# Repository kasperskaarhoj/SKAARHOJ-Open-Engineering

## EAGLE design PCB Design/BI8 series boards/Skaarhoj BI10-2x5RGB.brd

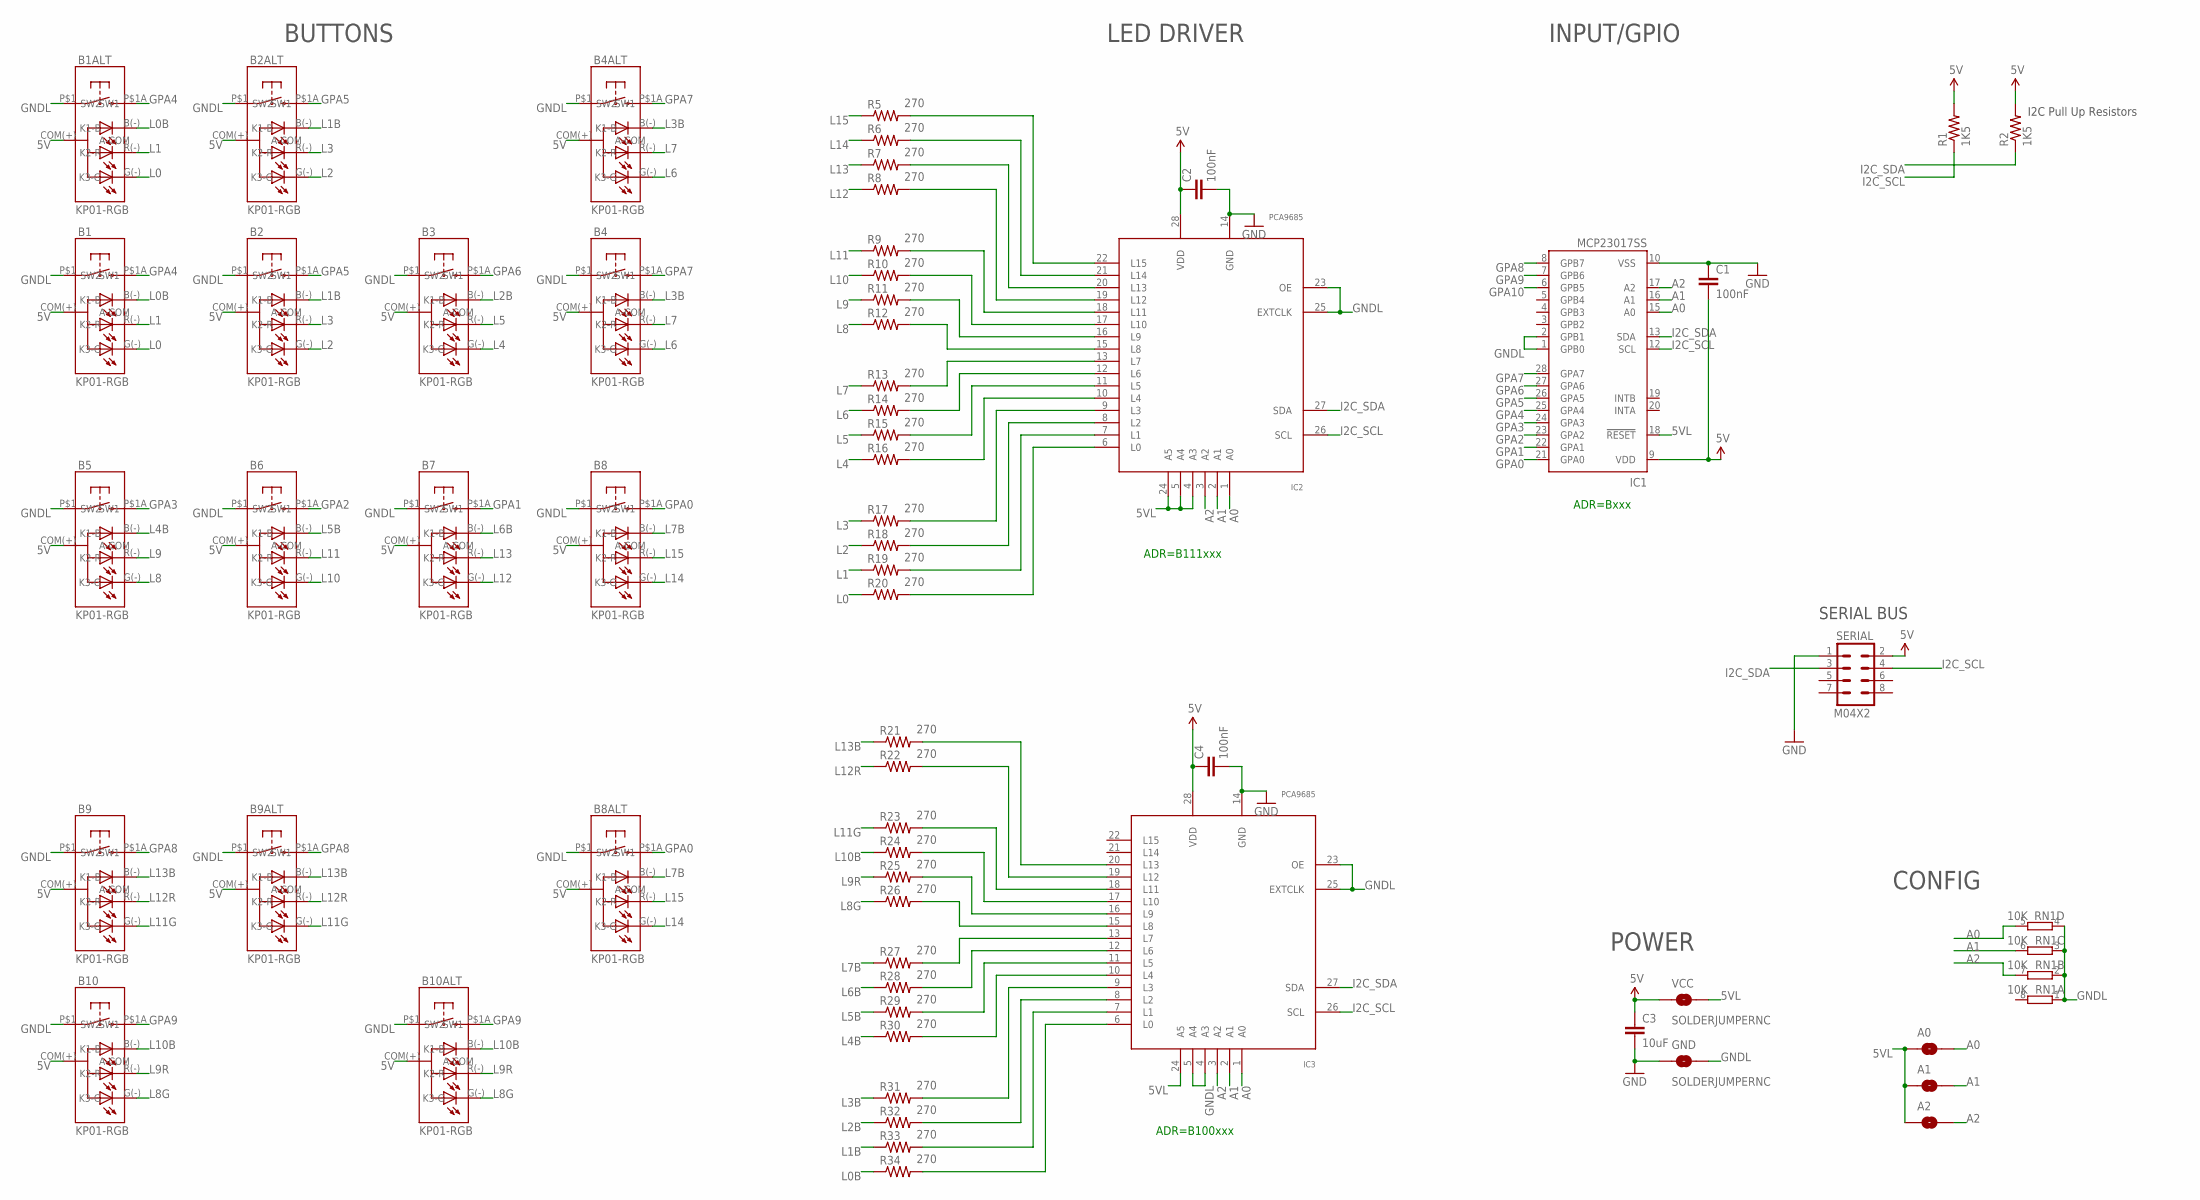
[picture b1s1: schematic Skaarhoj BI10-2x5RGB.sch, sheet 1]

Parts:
A0, A1, A2: SOLDERJUMPERNC; SJ_2S
B1, B1ALT, B2, B2ALT, B3, B4, B4ALT, B5, B6, B7, B8, B8ALT, B9, B9ALT, B10, B10ALT: KP01-RGB; NKK-KP01
C1, C2, C4: 100nF; 0603-CAP
C3: 10uF; 0805
GND: SOLDERJUMPERNC; SJ_2S
IC1: MCP23017SS; SSOP28; MPN MCP23017-E/SS
IC2, IC3: PCA9685; TSSOP28
R1, R2: 1K5; 0603-RES
R5, R6, R7, R8, R9, R10, R11, R12, R13, R14, R15, R16, R17, R18, R19, R20, R21, R22, R23, R24, R25, R26, R27, R28, R29, R30, R31, R32, R33, R34: 270; 0603-RES
RN1: 10K; CAY16_HAND
SERIAL: M04X2; 2X4
VCC: SOLDERJUMPERNC; SJ_2S

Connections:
5V: B1.COM(+) (A-COM), B1ALT.COM(+) (A-COM), B2.COM(+) (A-COM), B2ALT.COM(+) (A-COM), B3.COM(+) (A-COM), B4.COM(+) (A-COM), B4ALT.COM(+) (A-COM), B5.COM(+) (A-COM), B6.COM(+) (A-COM), B7.COM(+) (A-COM), B8.COM(+) (A-COM), B8ALT.COM(+) (A-COM), B9.COM(+) (A-COM), B9ALT.COM(+) (A-COM), B10.COM(+) (A-COM), B10ALT.COM(+) (A-COM), C1.2, C2.1, C3.1, C4.1, IC1.9 (VDD), IC2.28 (VDD), IC3.28 (VDD), R1.2, R2.2, SERIAL.2, VCC.1
5VL: A0.1, A1.1, A2.1, IC1.18 (!RESET), IC2.4 (A3), IC2.5 (A4), IC2.24 (A5), IC3.24 (A5), VCC.2
A0: A0.2, IC1.15 (A0), IC2.1 (A0), IC3.1 (A0), RN1.5 (2)
A1: A1.2, IC1.16 (A1), IC2.2 (A1), IC3.2 (A1), RN1.6 (2)
A2: A2.2, IC1.17 (A2), IC2.3 (A2), IC3.3 (A2), RN1.7 (2)
GND: C1.1, C2.2, C3.2, C4.2, GND.1, IC1.10 (VSS), IC2.14 (GND), IC3.14 (GND), SERIAL.1
GNDL: B1.P$1 (SW1), B1ALT.P$1 (SW1), B2.P$1 (SW1), B2ALT.P$1 (SW1), B3.P$1 (SW1), B4.P$1 (SW1), B4ALT.P$1 (SW1), B5.P$1 (SW1), B6.P$1 (SW1), B7.P$1 (SW1), B8.P$1 (SW1), B8ALT.P$1 (SW1), B9.P$1 (SW1), B9ALT.P$1 (SW1), B10.P$1 (SW1), B10ALT.P$1 (SW1), GND.2, IC1.1 (GPB0), IC1.2 (GPB1), IC2.23 (OE), IC2.25 (EXTCLK), IC3.4 (A3), IC3.5 (A4), IC3.23 (OE), IC3.25 (EXTCLK), RN1.1, RN1.2 (1), RN1.3 (1), RN1.4 (1)
GPA0: B8.P$1A (SW2), B8ALT.P$1A (SW2), IC1.21 (GPA0)
GPA1: B7.P$1A (SW2), IC1.22 (GPA1)
GPA2: B6.P$1A (SW2), IC1.23 (GPA2)
GPA3: B5.P$1A (SW2), IC1.24 (GPA3)
GPA4: B1.P$1A (SW2), B1ALT.P$1A (SW2), IC1.25 (GPA4)
GPA5: B2.P$1A (SW2), B2ALT.P$1A (SW2), IC1.26 (GPA5)
GPA6: B3.P$1A (SW2), IC1.27 (GPA6)
GPA7: B4.P$1A (SW2), B4ALT.P$1A (SW2), IC1.28 (GPA7)
GPA8: B9.P$1A (SW2), B9ALT.P$1A (SW2), IC1.8 (GPB7)
GPA9: B10.P$1A (SW2), B10ALT.P$1A (SW2), IC1.7 (GPB6)
GPA10: IC1.6 (GPB5)
I2C_SCL: IC1.12 (SCL), IC2.26 (SCL), IC3.26 (SCL), R1.1, SERIAL.4
I2C_SDA: IC1.13 (SDA), IC2.27 (SDA), IC3.27 (SDA), R2.1, SERIAL.3
L0: B1.G(-) (K3-G), B1ALT.G(-) (K3-G), R20.1
L0B: B1.B(-) (K1-B), B1ALT.B(-) (K1-B), R34.1
L1: B1.R(-) (K2-R), B1ALT.R(-) (K2-R), R19.1
L1B: B2.B(-) (K1-B), B2ALT.B(-) (K1-B), R33.1
L2: B2.G(-) (K3-G), B2ALT.G(-) (K3-G), R18.1
L2B: B3.B(-) (K1-B), R32.1
L3: B2.R(-) (K2-R), B2ALT.R(-) (K2-R), R17.1
L3B: B4.B(-) (K1-B), B4ALT.B(-) (K1-B), R31.1
L4: B3.G(-) (K3-G), R16.1
L4B: B5.B(-) (K1-B), R30.1
L5: B3.R(-) (K2-R), R15.1
L5B: B6.B(-) (K1-B), R29.1
L6: B4.G(-) (K3-G), B4ALT.G(-) (K3-G), R14.1
L6B: B7.B(-) (K1-B), R28.1
L7: B4.R(-) (K2-R), B4ALT.R(-) (K2-R), R13.1
L7B: B8.B(-) (K1-B), B8ALT.B(-) (K1-B), R27.1
L8: B5.G(-) (K3-G), R12.1
L8G: B10.G(-) (K3-G), B10ALT.G(-) (K3-G), R26.1
L9: B5.R(-) (K2-R), R11.1
L9R: B10.R(-) (K2-R), B10ALT.R(-) (K2-R), R25.1
L10: B6.G(-) (K3-G), R10.1
L10B: B10.B(-) (K1-B), B10ALT.B(-) (K1-B), R24.1
L11: B6.R(-) (K2-R), R9.1
L11G: B9.G(-) (K3-G), B9ALT.G(-) (K3-G), R23.1
L12: B7.G(-) (K3-G), R8.1
L12R: B9.R(-) (K2-R), B9ALT.R(-) (K2-R), R22.1
L13: B7.R(-) (K2-R), R7.1
L13B: B9.B(-) (K1-B), B9ALT.B(-) (K1-B), R21.1
L14: B8.G(-) (K3-G), B8ALT.G(-) (K3-G), R6.1
L15: B8.R(-) (K2-R), B8ALT.R(-) (K2-R), R5.1
unnamed: IC3.13 (L7), R27.2
unnamed: IC3.12 (L6), R28.2
unnamed: IC2.13 (L7), R13.2
unnamed: IC2.12 (L6), R14.2
unnamed: IC3.11 (L5), R29.2
unnamed: IC2.11 (L5), R15.2
unnamed: IC2.10 (L4), R16.2
unnamed: IC2.9 (L3), R17.2
unnamed: IC2.8 (L2), R18.2
unnamed: IC2.7 (L1), R19.2
unnamed: IC3.10 (L4), R30.2
unnamed: IC3.9 (L3), R31.2
unnamed: IC3.8 (L2), R32.2
unnamed: IC3.7 (L1), R33.2
unnamed: IC3.6 (L0), R34.2
unnamed: IC3.15 (L8), R26.2
unnamed: IC2.6 (L0), R20.2
unnamed: IC2.15 (L8), R12.2
unnamed: IC2.16 (L9), R11.2
unnamed: IC2.17 (L10), R10.2
unnamed: IC2.18 (L11), R9.2
unnamed: IC2.19 (L12), R8.2
unnamed: IC2.20 (L13), R7.2
unnamed: IC2.21 (L14), R6.2
unnamed: IC2.22 (L15), R5.2
unnamed: IC3.16 (L9), R25.2
unnamed: IC3.17 (L10), R24.2
unnamed: IC3.18 (L11), R23.2
unnamed: IC3.19 (L12), R22.2
unnamed: IC3.20 (L13), R21.2

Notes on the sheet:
I2C Pull Up Resistors
SERIAL BUS
ADR=B111xxx
ADR=Bxxx
BUTTONS
LED DRIVER
INPUT/GPIO
POWER
CONFIG
ADR=B100xxx

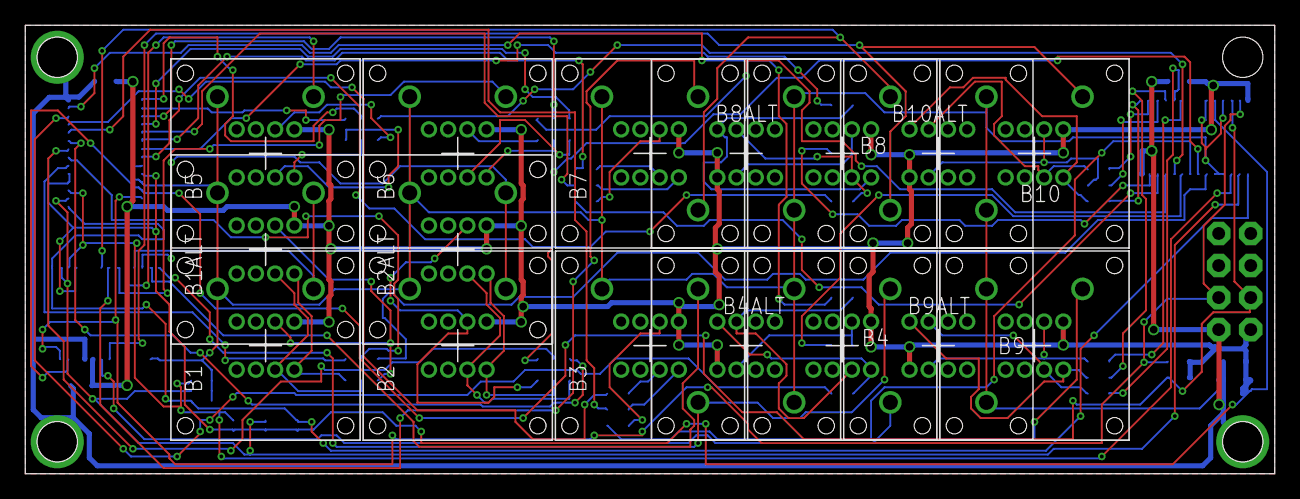
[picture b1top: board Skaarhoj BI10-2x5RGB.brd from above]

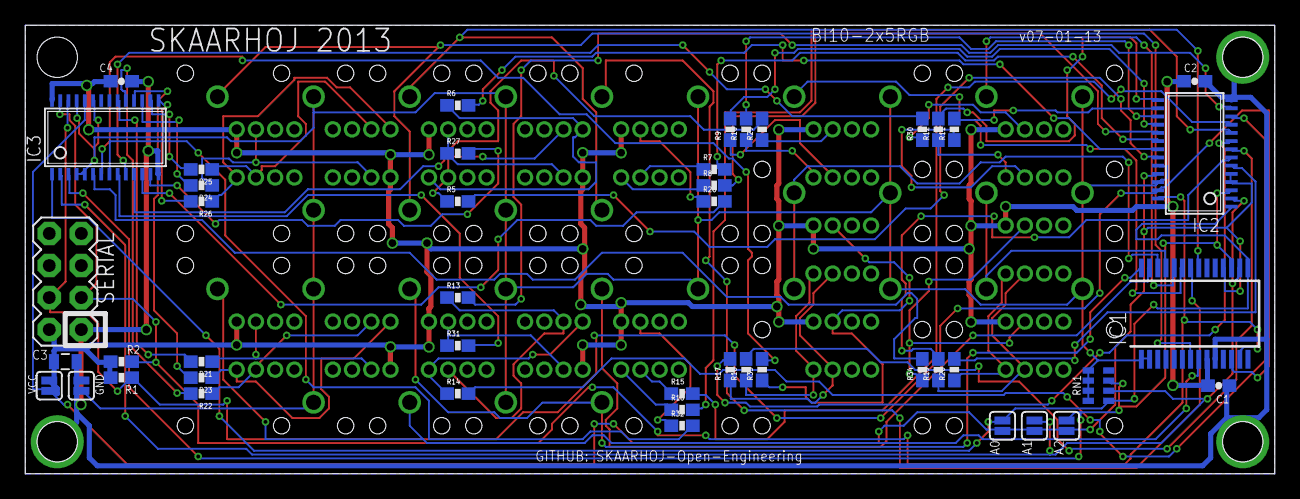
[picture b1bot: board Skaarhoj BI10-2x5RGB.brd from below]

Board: 2 copper layers, 99.1 x 35.6 mm, 62 parts (46 on the bottom side), 79 nets.

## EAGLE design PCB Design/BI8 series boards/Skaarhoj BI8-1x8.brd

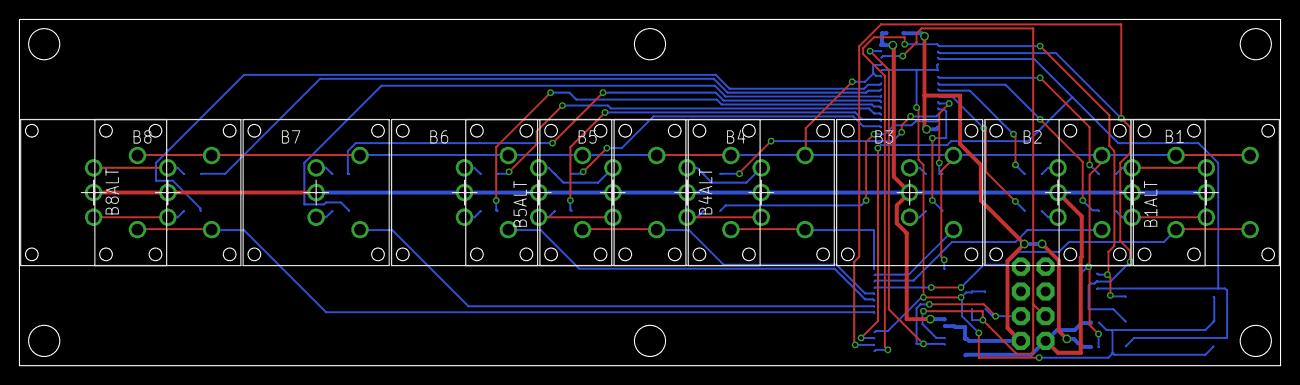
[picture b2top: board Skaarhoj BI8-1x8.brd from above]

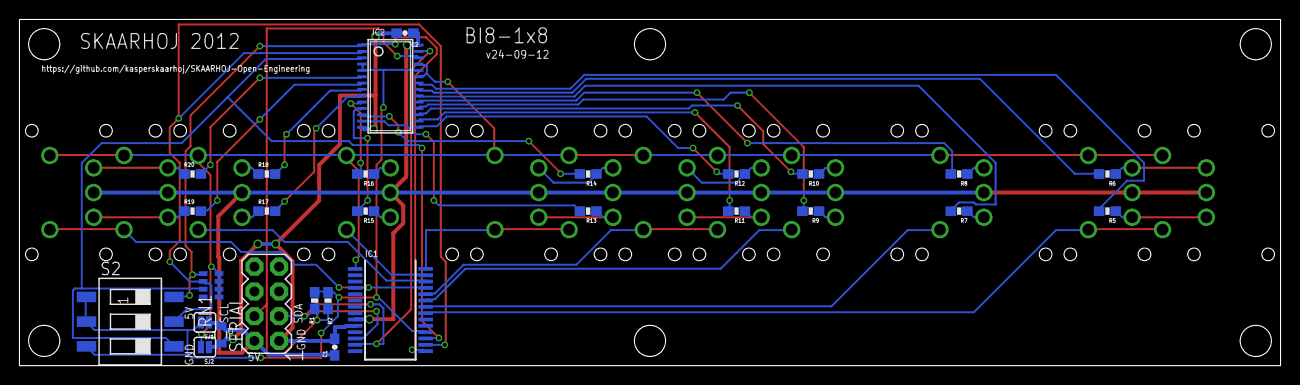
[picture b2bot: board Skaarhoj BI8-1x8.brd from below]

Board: 2 copper layers, 129.5 x 35.6 mm, 40 parts (28 on the bottom side), 49 nets.

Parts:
B1, B1ALT, B2, B3, B4, B4ALT, B5, B5ALT, B6, B7, B8, B8ALT: LP11-B"; LP11
C1, C2: 100nF; 0603-CAP
C3: 10uF; 0805
IC1: MCP23017SS; SSOP28
IC2: PCA9685; TSSOP28
R1, R2: 10K; 0603-RES
R5, R6, R7, R8, R9, R10, R11, R12, R13, R14, R15, R16, R17, R18, R19, R20: 270; 0603-RES
RN1: 10K; CAY16_HAND
S2: SWS003; SMS-003
SERIAL: M04X2; 2X4
SJ1, SJ2: SOLDERJUMPERNC; SJ_2S

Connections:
5V: B1.COM, B1ALT.COM, B2.COM, B3.COM, B4.COM, B4ALT.COM, B5.COM, B5ALT.COM, B6.COM, B7.COM, B8.COM, B8ALT.COM, C1.2, C2.1, C3.1, IC1.9, IC2.28, SERIAL.2, SJ1.1
5VL: IC1.18, IC2.4, IC2.5, IC2.24, R1.1, R2.1, S2.1, S2.2, S2.3, SJ1.2
A0: IC1.15, IC2.1, RN1.5, S2.6
A1: IC1.16, IC2.2, RN1.6, S2.5
A2: IC1.17, IC2.3, RN1.7, S2.4
GND: C1.1, C2.2, C3.2, IC1.10, IC2.14, SERIAL.1, SJ2.1
GNDL: B1.P$4, B1ALT.P$4, B2.P$4, B3.P$4, B4.P$4, B4ALT.P$4, B5.P$4, B5ALT.P$4, B6.P$4, B7.P$4, B8.P$4, B8ALT.P$4, IC1.1, IC2.23, IC2.25, RN1.1, RN1.2, RN1.3, RN1.4, SJ2.2
GPA0: B8.P$5, B8ALT.P$5, IC1.21
GPA1: B7.P$5, IC1.22
GPA2: B6.P$5, IC1.23
GPA3: B5.P$5, B5ALT.P$5, IC1.24
GPA4: B1.P$5, B1ALT.P$5, IC1.25
GPA5: B2.P$5, IC1.26
GPA6: B3.P$5, IC1.27
GPA7: B4.P$5, B4ALT.P$5, IC1.28
I2C_SCL: IC1.12, IC2.26, R2.2, SERIAL.4
I2C_SDA: IC1.13, IC2.27, R1.2, SERIAL.3
L0: B1.P$2, B1ALT.P$2, R20.1
L1: B1.P$3, B1ALT.P$3, R19.1
L2: B2.P$2, R18.1
L3: B2.P$3, R17.1
L4: B3.P$2, R16.1
L5: B3.P$3, R15.1
L6: B4.P$2, B4ALT.P$2, R14.1
L7: B4.P$3, B4ALT.P$3, R13.1
L8: B5.P$2, B5ALT.P$2, R12.1
L9: B5.P$3, B5ALT.P$3, R11.1
L10: B6.P$2, R10.1
L11: B6.P$3, R9.1
L12: B7.P$2, R8.1
L13: B7.P$3, R7.1
L14: B8.P$2, B8ALT.P$2, R6.1
L15: B8.P$3, B8ALT.P$3, R5.1
unnamed: IC2.13, R13.2
unnamed: IC2.12, R14.2
unnamed: IC2.11, R15.2
unnamed: IC2.10, R16.2
unnamed: IC2.9, R17.2
unnamed: IC2.8, R18.2
unnamed: IC2.7, R19.2
unnamed: IC2.6, R20.2
unnamed: IC2.15, R12.2
unnamed: IC2.16, R11.2
unnamed: IC2.17, R10.2
unnamed: IC2.18, R9.2
unnamed: IC2.19, R8.2
unnamed: IC2.20, R7.2
unnamed: IC2.21, R6.2
unnamed: IC2.22, R5.2

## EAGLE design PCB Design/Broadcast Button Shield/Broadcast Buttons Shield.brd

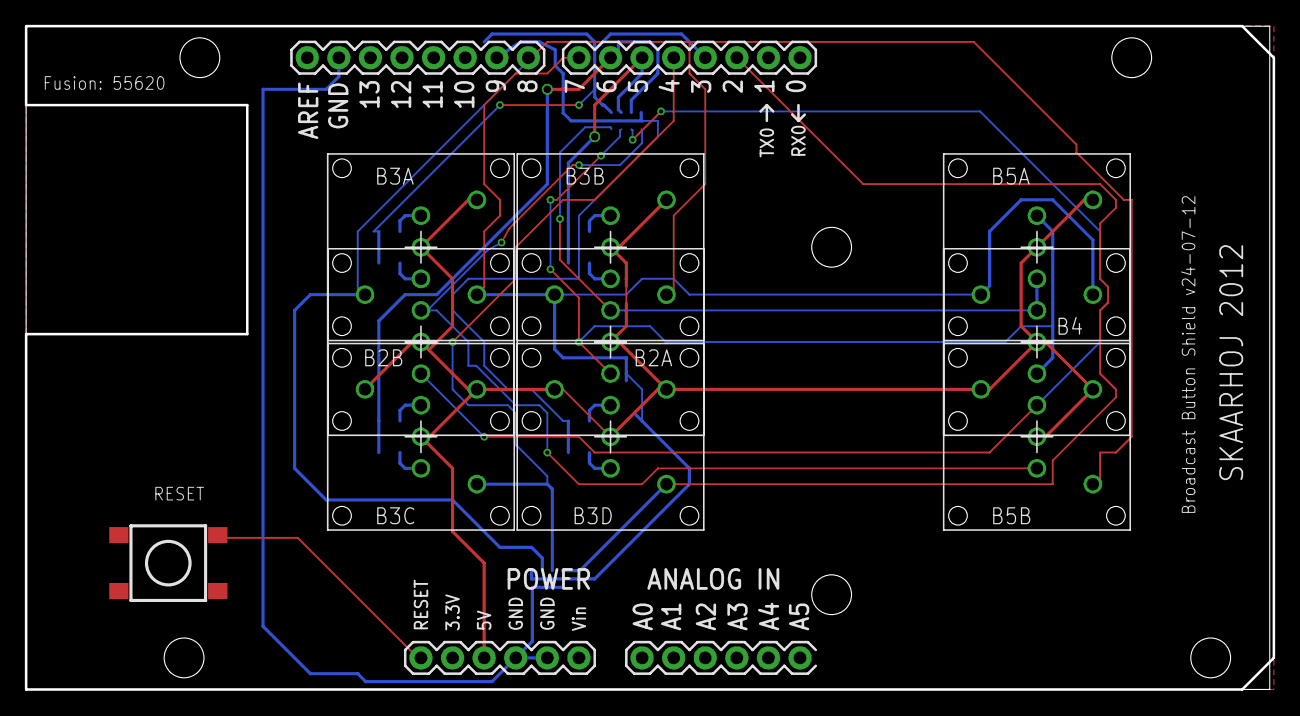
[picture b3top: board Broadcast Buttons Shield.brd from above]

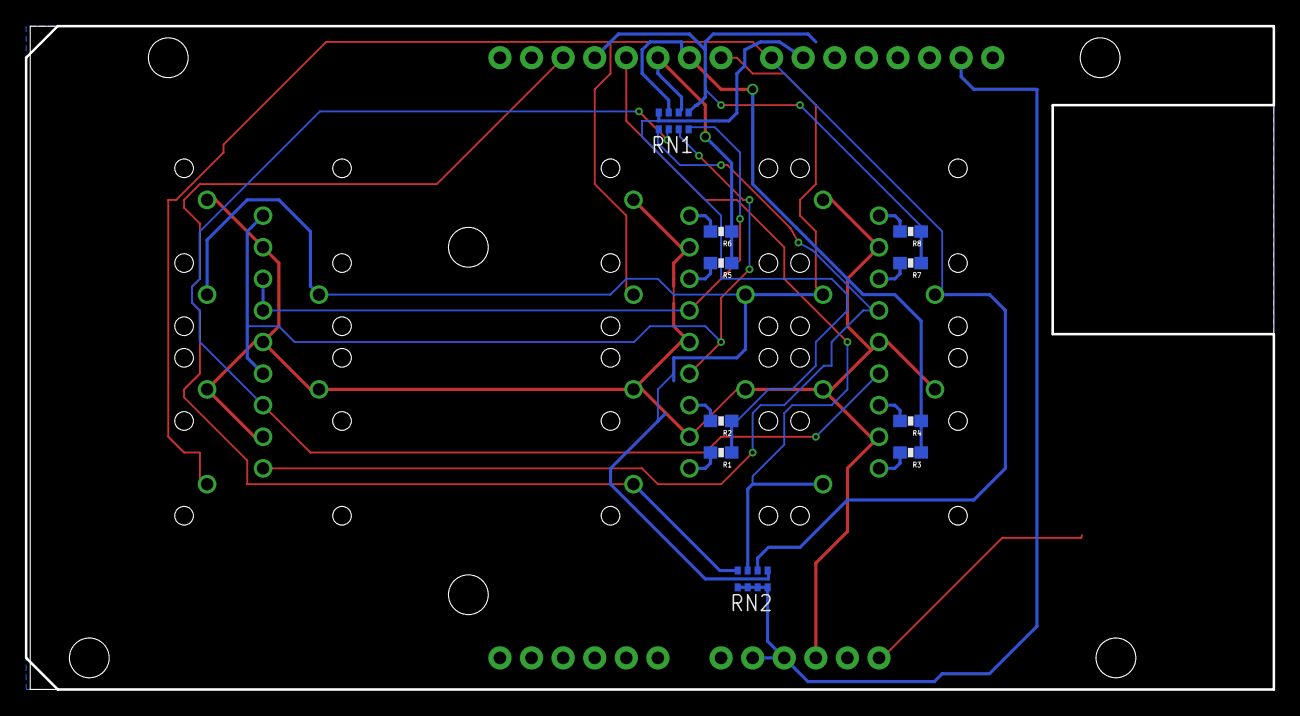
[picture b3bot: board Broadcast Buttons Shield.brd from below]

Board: 2 copper layers, 100.3 x 53.3 mm, 21 parts (10 on the bottom side), 23 nets.

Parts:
B2A, B2B, B3A, B3B, B3C, B3D, B4, B5A, B5B: LP11-B"; LP11
R1, R2, R3, R4, R5, R6, R7, R8: 0603-RES
RN1: 220; CAY16
RN2: 10K; CAY16
S1: SWITCH-MOMENTARY-2; TACTILE_SWITCH_TALL
U1: ARDUINO_SHIELDBOXSHIELD; ARDUINO_BOXSHIELD

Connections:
5V: B2A.COM, B2A.P$4, B2B.COM, B2B.P$4, B3A.COM, B3A.P$4, B3B.COM, B3B.P$4, B3C.COM, B3C.P$4, B3D.COM, B3D.P$4, B4.COM, B4.P$4, B5A.COM, B5A.P$4, B5B.COM, B5B.P$4, U1.5V@0
GND: RN2.1, RN2.2, RN2.3, RN2.4, S1.A2, U1.GND@0, U1.GND@1, U1.GND@4
unnamed: B3D.P$3, R1.2
unnamed: B2A.P$3, B4.P$3, B5A.P$3, RN1.4
unnamed: B3D.P$2, R2.2
unnamed: B3C.P$3, R3.2
unnamed: B3C.P$2, R4.2
unnamed: B3C.P$5, RN2.7, U1.4
unnamed: R5.1, R6.1, RN1.6, U1.5
unnamed: R3.1, R4.1, RN1.7, U1.6
unnamed: R1.1, R2.1, RN1.8, U1.9
unnamed: B2B.P$5, B3B.P$5, B5B.P$5, RN2.6, U1.8
unnamed: B2A.P$2, B4.P$2, B5A.P$2, RN1.3
unnamed: B2B.P$2, B5B.P$2, RN1.2
unnamed: B2B.P$3, B5B.P$3, RN1.1
unnamed: B2A.P$5, B3A.P$5, B4.P$5, B5A.P$5, RN2.5, U1.7
unnamed: B3B.P$3, R5.2
unnamed: B3B.P$2, R6.2
unnamed: B3A.P$3, R7.2
unnamed: B3A.P$2, R8.2
unnamed: B3D.P$5, RN2.8, U1.2
unnamed: R7.1, R8.1, RN1.5, U1.3
unnamed: S1.B2, U1.RESET

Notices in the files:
parts and their libraries:
SparkFun: Licensing: CC v3.0 Share-Alike You are welcome to use this library for commercial purposes.
